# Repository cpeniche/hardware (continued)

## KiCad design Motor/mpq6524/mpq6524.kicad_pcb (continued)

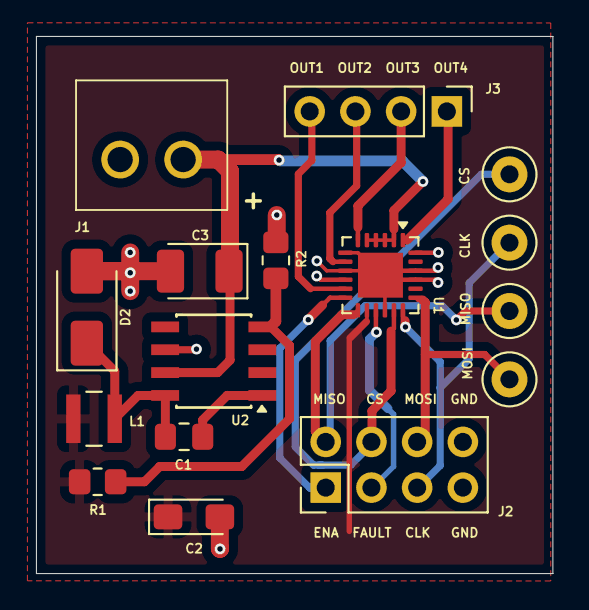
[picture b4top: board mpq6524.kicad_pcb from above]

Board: 2 copper layers, 28.7 x 29.8 mm, 16 parts (0 on the bottom side), 16 nets.

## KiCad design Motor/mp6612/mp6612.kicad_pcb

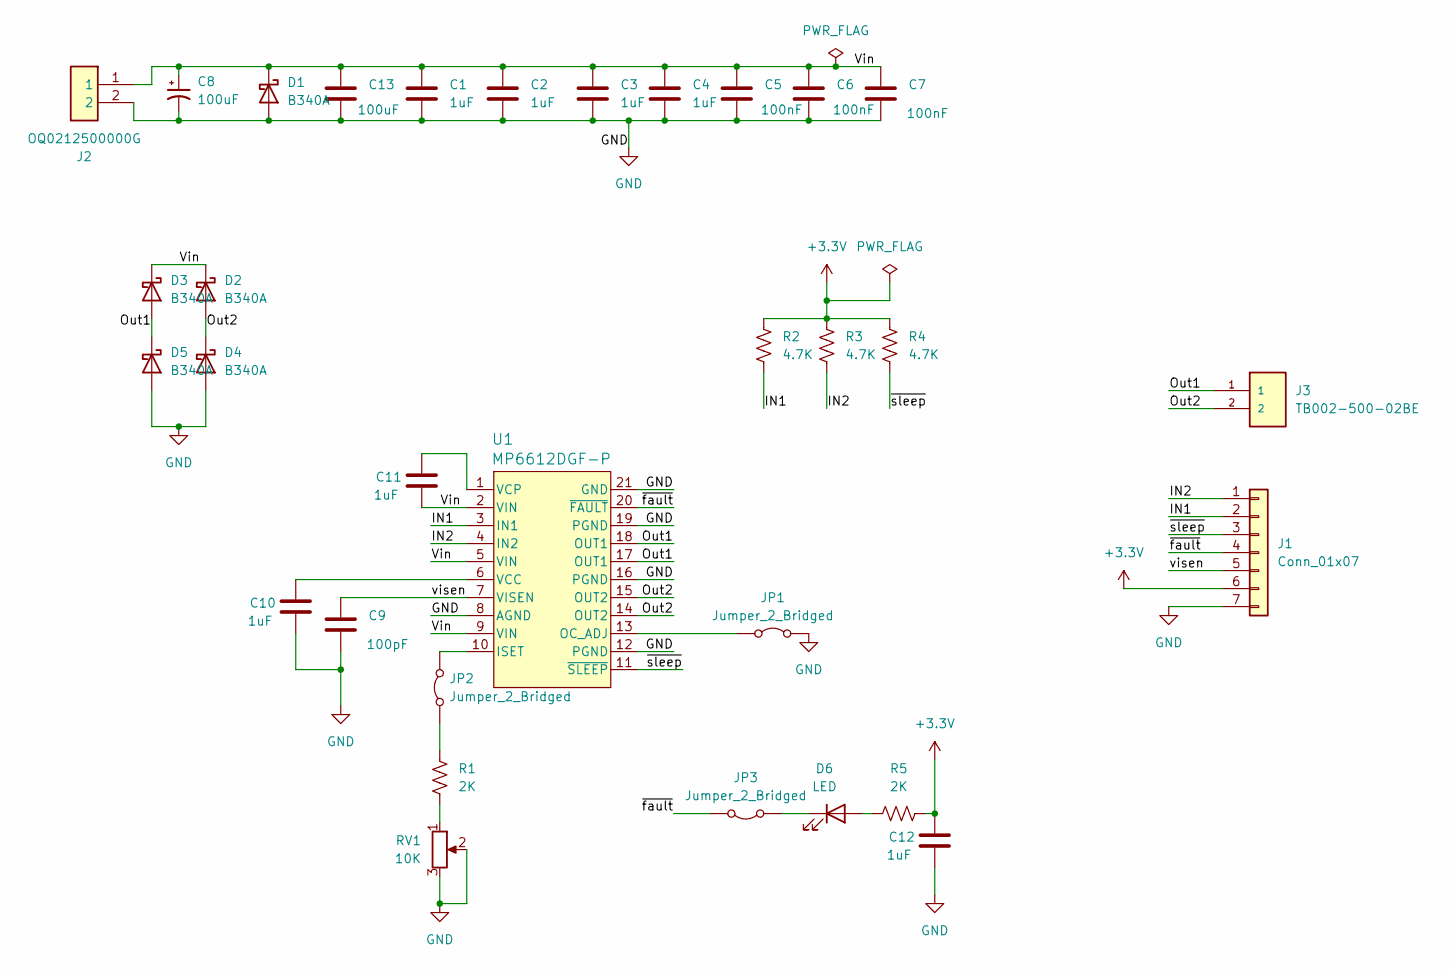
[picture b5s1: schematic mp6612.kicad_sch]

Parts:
C1, C2, C3, C4, C10, C11, C12: 1uF; C_0805_2012Metric_Pad1.18x1.45mm_HandSolder
C5, C6, C7: 100nF; C_0805_2012Metric_Pad1.18x1.45mm_HandSolder
C8: 100uF; CP_EIA-3216-18_Kemet-A_HandSolder
C9: 100pF; C_0805_2012Metric_Pad1.18x1.45mm_HandSolder
C13: 100uF; C_0805_2012Metric_Pad1.18x1.45mm_HandSolder
D1, D2, D3, D4, D5: B340A; D_SMA
D6: LED; LED_0402_1005Metric_Pad0.77x0.64mm_HandSolder
J1: Conn_01x07; PinHeader_1x07_P2.54mm_Vertical
J2: OQ0212500000G; Mouser Part Number 649-220107-C021A01LF
J3: TB002-500-02BE; CUI_TB002-500-02BE
JP1, JP2, JP3: Jumper_2_Bridged; TestPoint_2Pads_Pitch2.54mm_Drill0.8mm
R1, R5: 2K; R_0805_2012Metric_Pad1.20x1.40mm_HandSolder
R2, R3, R4: 4.7K; R_0805_2012Metric_Pad1.20x1.40mm_HandSolder
RV1: 10K; Potentiometer_Runtron_RM-065_Vertical
U1: MP6612DGF-P; TSSOP-20EP_MP6612D_MNP

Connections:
+3.3V: C12.1, J1.6, R2.2, R3.2, R4.2, R5.1
/IN1: J1.2, R2.1, U1.3 (IN1)
/IN2: J1.1, R3.1, U1.4 (IN2)
/Out1: D3.2 (A), D5.1 (K), J3.1, U1.17 (OUT1), U1.18 (OUT1)
/Out2: D2.2 (A), D4.1 (K), J3.2, U1.14 (OUT2), U1.15 (OUT2)
/Vin: C1.1, C2.1, C3.1, C4.1, C5.1, C6.1, C7.1, C8.1, C11.2, C13.1, D1.1 (K), D2.1 (K), D3.1 (K), J2.1, U1.2 (VIN), U1.5 (VIN), U1.9 (VIN)
/visen: C9.1, J1.5, U1.7 (VISEN)
/~fault: J1.4, JP3.2 (B), U1.20 (~FAULT)
/~sleep: J1.3, R4.1, U1.11 (~SLEEP)
GND: C1.2, C2.2, C3.2, C4.2, C5.2, C6.2, C7.2, C8.2, C9.2, C10.2, C12.2, C13.2, D1.2 (A), D4.2 (A), D5.2 (A), J1.7, J2.2, JP1.2 (B), RV1.2, RV1.3, U1.8 (AGND), U1.12 (PGND), U1.16 (PGND), U1.19 (PGND), U1.21 (GND)
unnamed: D6.2 (A), R5.2
unnamed: D6.1 (K), JP3.1 (A)
unnamed: JP1.1 (A), U1.13 (OC_ADJ)
unnamed: JP2.1 (A), R1.2
unnamed: JP2.2 (B), U1.10 (ISET)
unnamed: R1.1, RV1.1
unnamed: C10.1, U1.6 (VCC)
unnamed: C11.1, U1.1 (VCP)

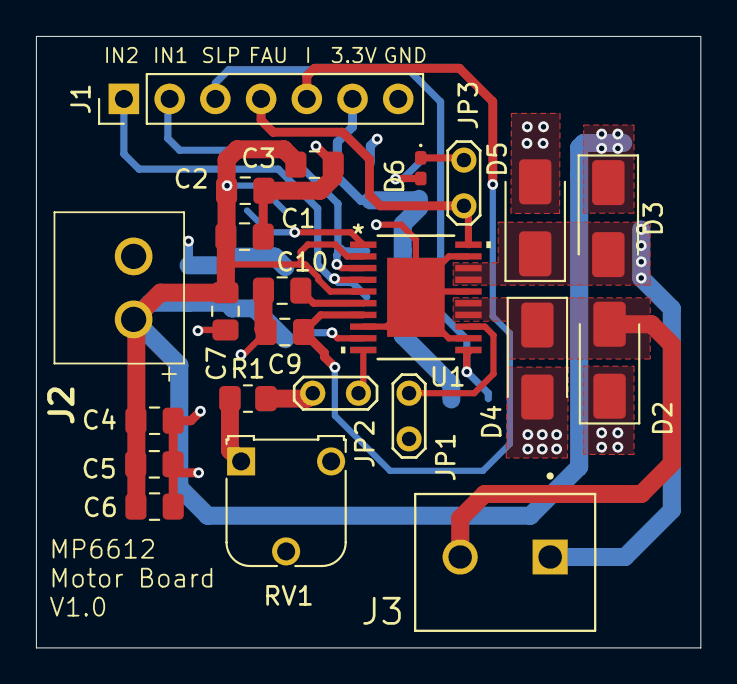
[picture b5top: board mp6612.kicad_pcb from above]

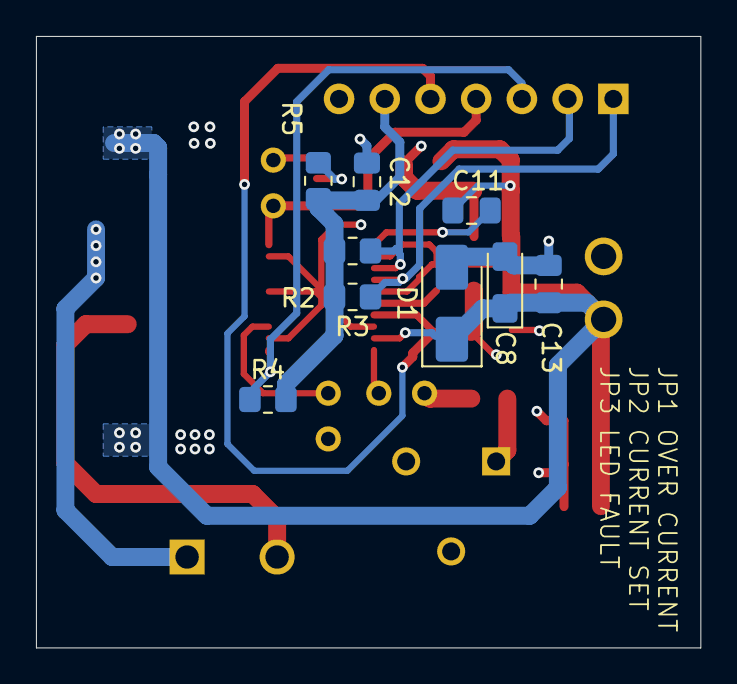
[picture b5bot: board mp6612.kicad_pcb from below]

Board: 4 copper layers, 36.9 x 34.0 mm, 32 parts (9 on the bottom side), 18 nets.

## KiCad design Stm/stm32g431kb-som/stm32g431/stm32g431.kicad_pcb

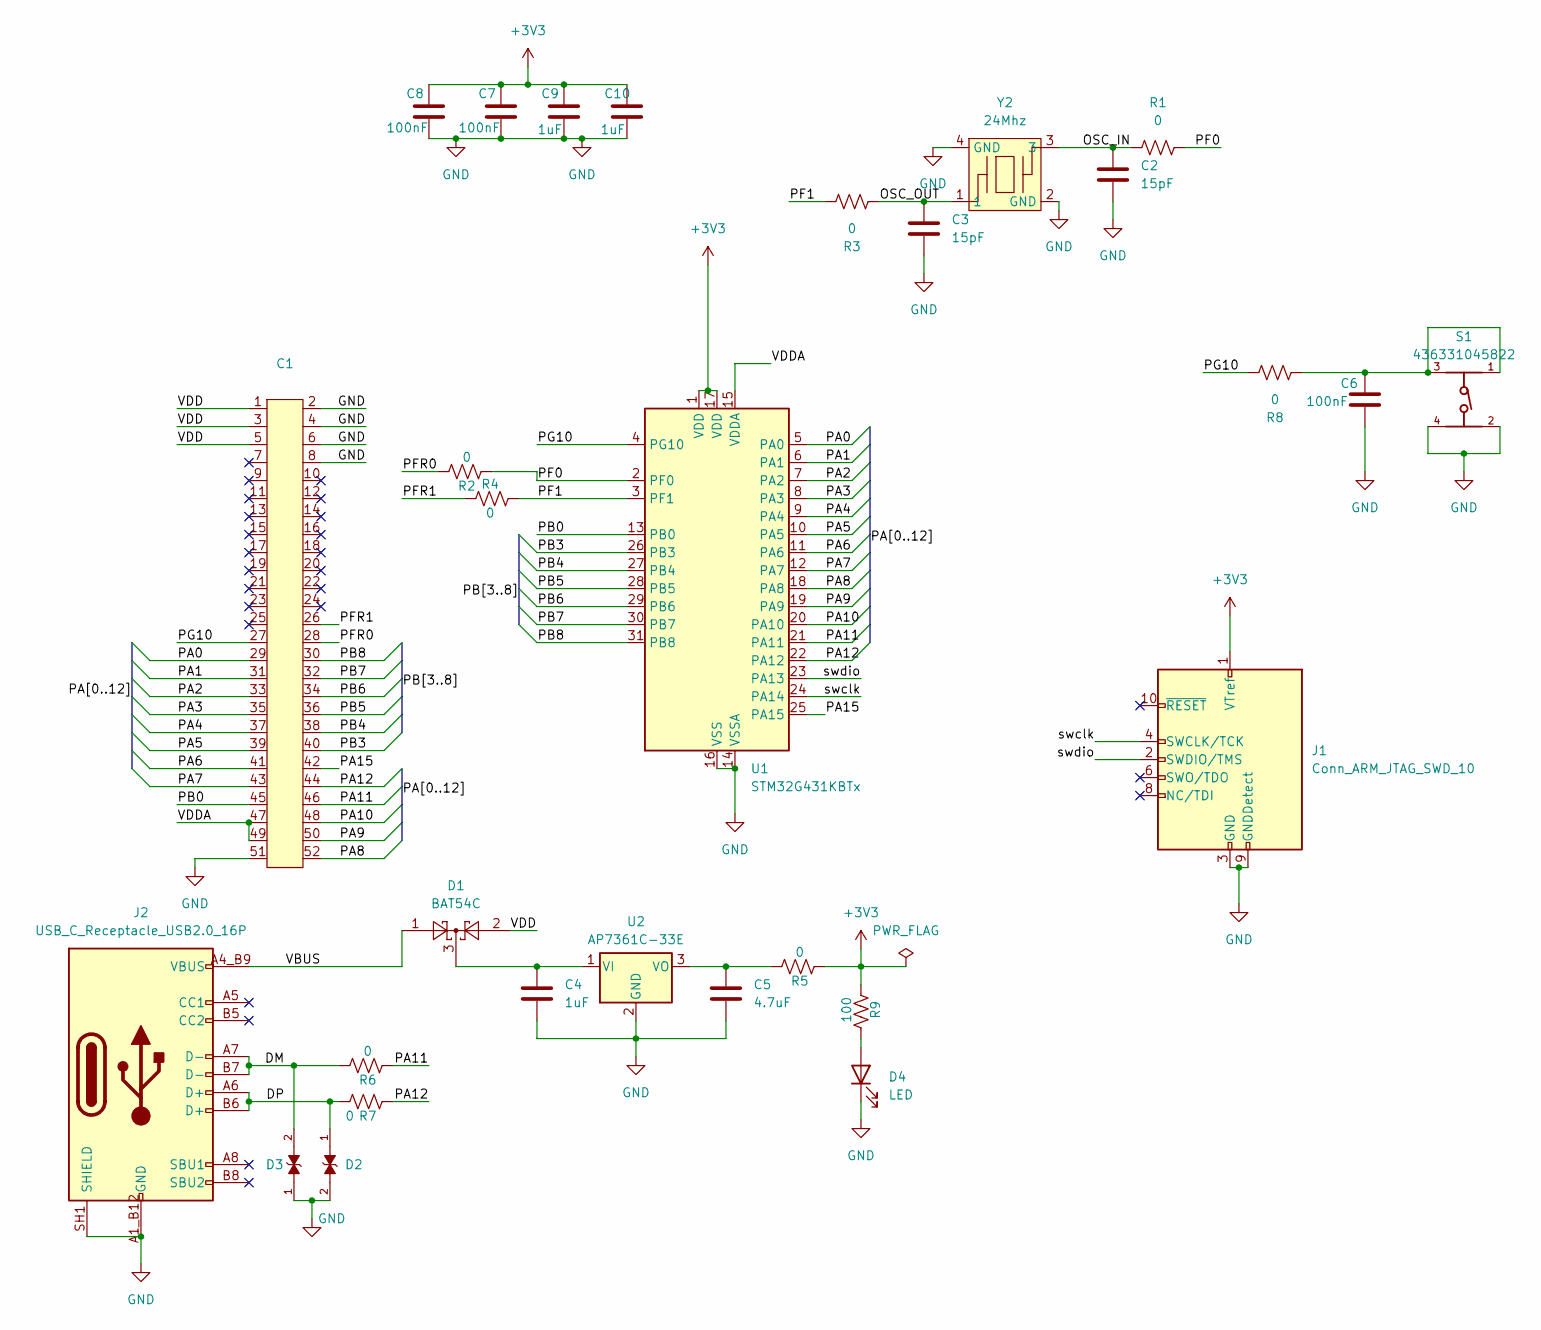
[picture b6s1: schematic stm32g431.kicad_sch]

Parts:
C1: Mini PCI express Half
C2, C3: 15pF; C_0402_1005Metric_Pad0.74x0.62mm_HandSolder
C4, C9, C10: 1uF; C_0402_1005Metric_Pad0.74x0.62mm_HandSolder
C5: 4.7uF; C_0402_1005Metric_Pad0.74x0.62mm_HandSolder
C6, C7, C8: 100nF; C_0402_1005Metric_Pad0.74x0.62mm_HandSolder
D1: BAT54C; SOT-23
D2, D3: PGB1010603NR; DIOC1608X36N
D4: LED; LED_0402_1005Metric
J1: Conn_ARM_JTAG_SWD_10; PinHeader_2x05_P1.27mm_Vertical_SMD
J2: USB_C_Receptacle_USB2.0_16P; AMPHENOL_GSB1C41110SSHR; PARTREV AX1
R1, R2, R3, R4, R5, R6, R7, R8: 0; R_0402_1005Metric_Pad0.72x0.64mm_HandSolder
R9: 100; R_0402_1005Metric_Pad0.72x0.64mm_HandSolder
S1: 436331045822; 4363X10458XX
U1: STM32G431KBTx; LQFP-32_7x7mm_P0.8mm
U2: AP7361C-33E; SOT-223-3_TabPin2
Y2: 24Mhz; jxs11

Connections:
+3V3: C7.1, C8.1, C9.1, C10.1, J1.1 (VTref), R5.2, R9.2, U1.1 (VDD), U1.17 (VDD)
/DM: D3.2, J2.A7 (D-), J2.B7 (D-), R6.1
/DP: D2.1, J2.A6 (D+), J2.B6 (D+), R7.1
/OSC_IN: C2.1, R1.1, Y2.3
/OSC_OUT: C3.1, R3.1, Y2.1
/PA0: C1.29, U1.5 (PA0)
/PA1: C1.31, U1.6 (PA1)
/PA2: C1.33, U1.7 (PA2)
/PA3: C1.35, U1.8 (PA3)
/PA4: C1.37, U1.9 (PA4)
/PA5: C1.39, U1.10 (PA5)
/PA6: C1.41, U1.11 (PA6)
/PA7: C1.43, U1.12 (PA7)
/PA8: C1.52, U1.18 (PA8)
/PA9: C1.50, U1.19 (PA9)
/PA10: C1.48, U1.20 (PA10)
/PA11: C1.46, R6.2, U1.21 (PA11)
/PA12: C1.44, R7.2, U1.22 (PA12)
/PA15: C1.42, U1.25 (PA15)
/PB0: C1.45, U1.13 (PB0)
/PB3: C1.40, U1.26 (PB3)
/PB4: C1.38, U1.27 (PB4)
/PB5: C1.36, U1.28 (PB5)
/PB6: C1.34, U1.29 (PB6)
/PB7: C1.32, U1.30 (PB7)
/PB8: C1.30, U1.31 (PB8)
/PF0: R1.2, R2.2, U1.2 (PF0)
/PF1: R3.2, R4.1, U1.3 (PF1)
/PFR0: C1.28, R2.1
/PFR1: C1.26, R4.2
/PG10: C1.27, R8.2, U1.4 (PG10)
/VBUS: D1.1, J2.A4_B9 (VBUS), J2.B4_A9 (VBUS)
/VDD: C1.1, C1.3, C1.5, D1.2
/VDDA: C1.47, C1.49, U1.15 (VDDA)
/swclk: J1.4 (SWCLK/TCK), U1.24 (PA14)
/swdio: J1.2 (SWDIO/TMS), U1.23 (PA13)
GND: C1.2, C1.4, C1.6, C1.8, C1.51, C2.2, C3.2, C4.2, C5.2, C6.2, C7.2, C8.2, C9.2, C10.2, D2.2, D3.1, D4.1 (K), J1.3 (GND), J1.5 (GND), J1.9 (GNDDetect), J2.A1_B12 (GND), J2.B1_A12 (GND), J2.SH1 (SHIELD), S1.2, S1.4, U1.14 (VSSA), U1.16 (VSS), U1.32 (VSS), U2.2 (GND), Y2.2 (GND), Y2.4 (GND)
unnamed: C6.1, R8.1, S1.1, S1.3
unnamed: D4.2 (A), R9.1
unnamed: C4.1, D1.3, U2.1 (VI)
unnamed: C5.1, R5.1, U2.3 (VO)

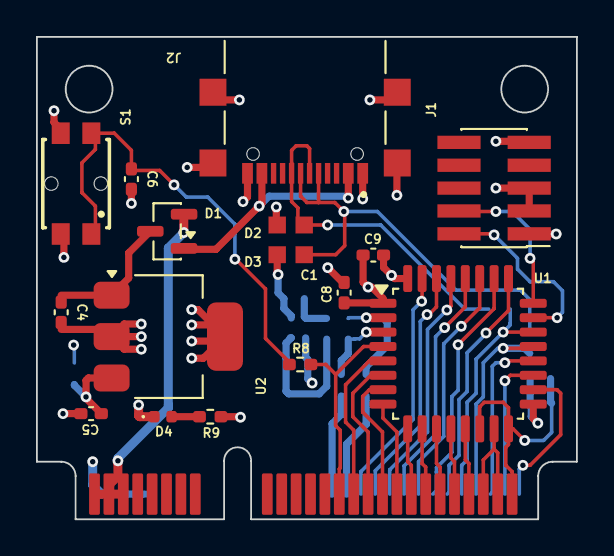
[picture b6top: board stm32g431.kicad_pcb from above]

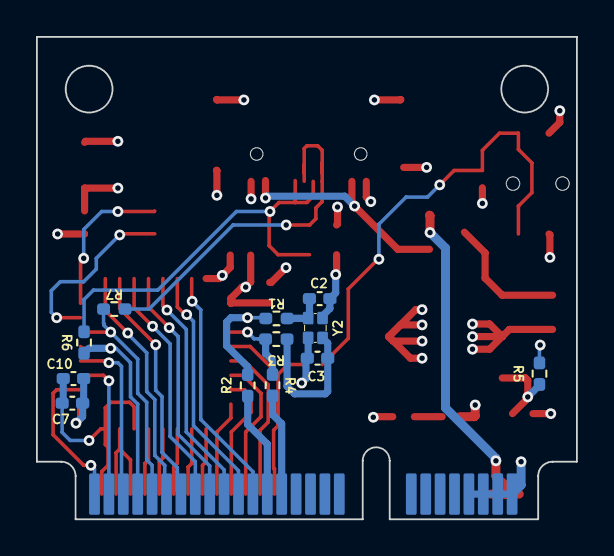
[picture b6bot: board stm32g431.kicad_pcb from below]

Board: 4 copper layers, 30.0 x 26.8 mm, 29 parts (12 on the bottom side), 41 nets.

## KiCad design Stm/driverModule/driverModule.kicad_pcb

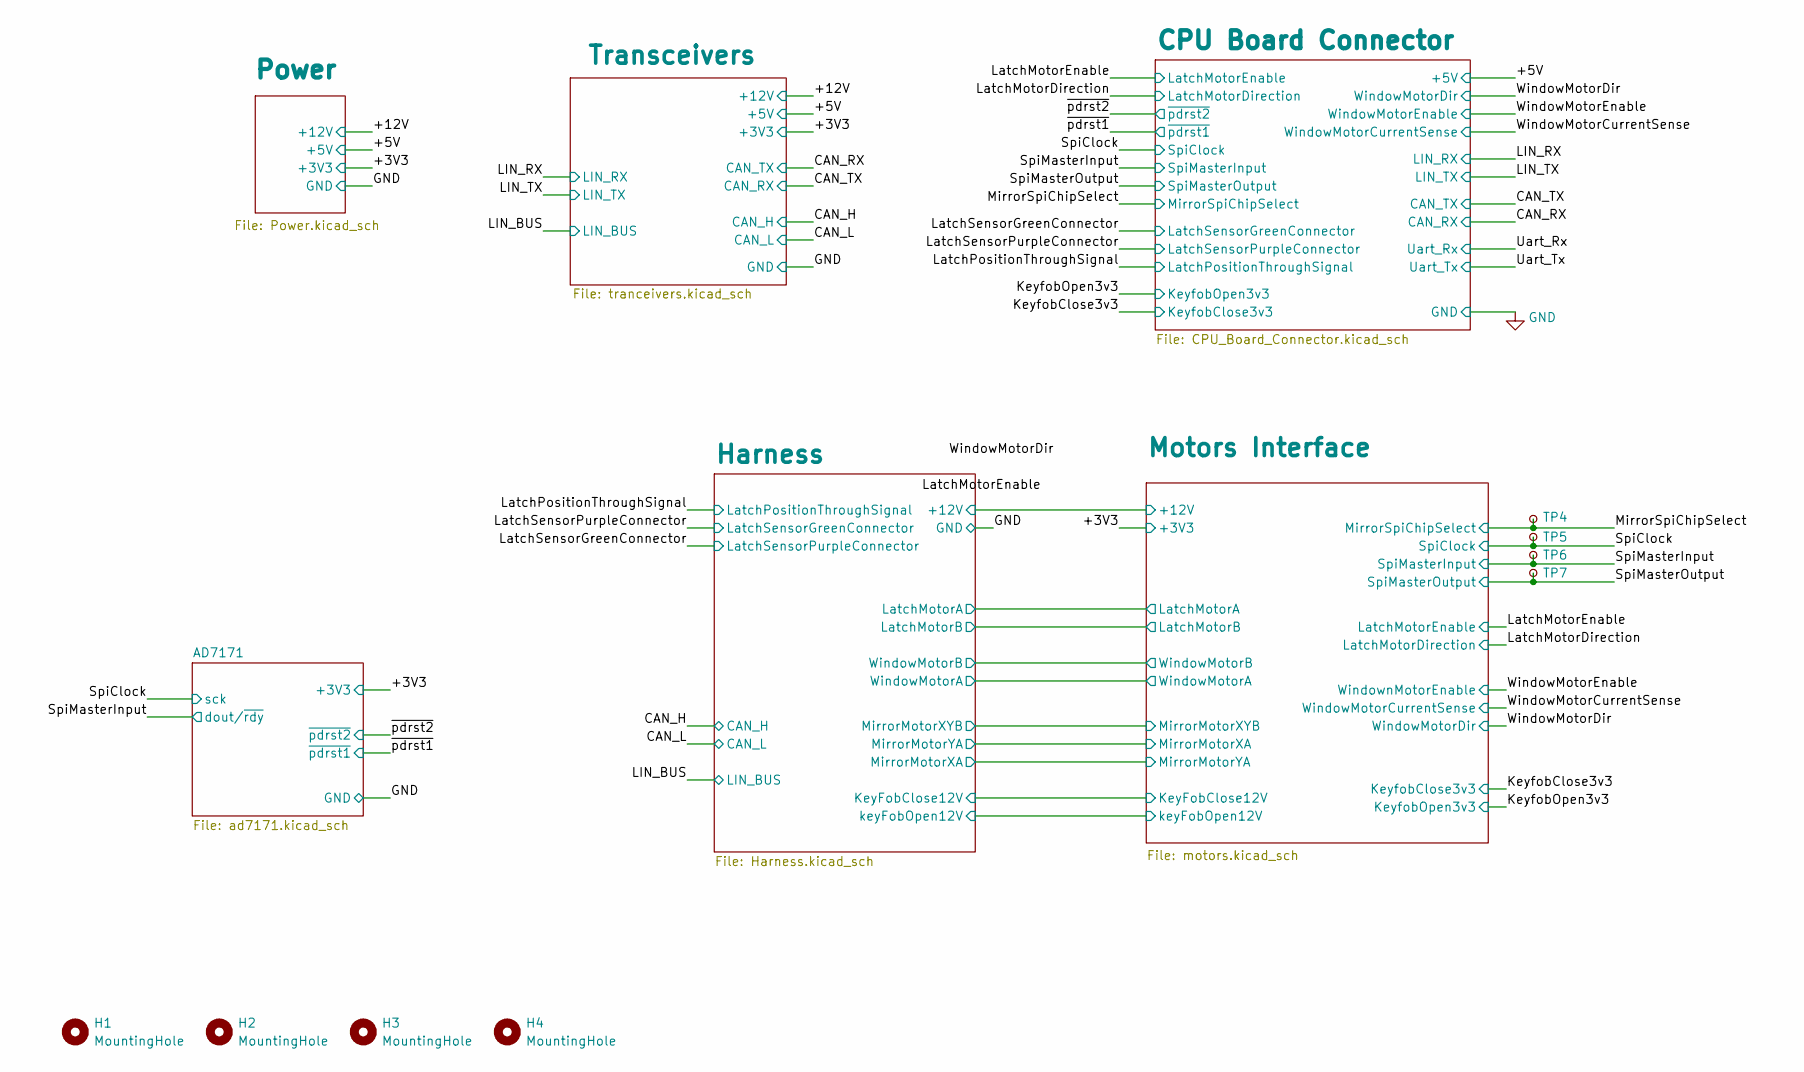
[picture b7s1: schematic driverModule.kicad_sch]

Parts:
H1, H2, H3, H4: MountingHole; MountingHole_2.2mm_M2
TP4, TP5, TP6, TP7: TestPoint_Small; TestPoint_Pad_1.0x1.0mm

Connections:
/MirrorSpiChipSelect: TP4.1; also elsewhere on the board
/SpiClock: TP5.1; also elsewhere on the board
/SpiMasterInput: TP6.1; also elsewhere on the board
/SpiMasterOutput: TP7.1; also elsewhere on the board

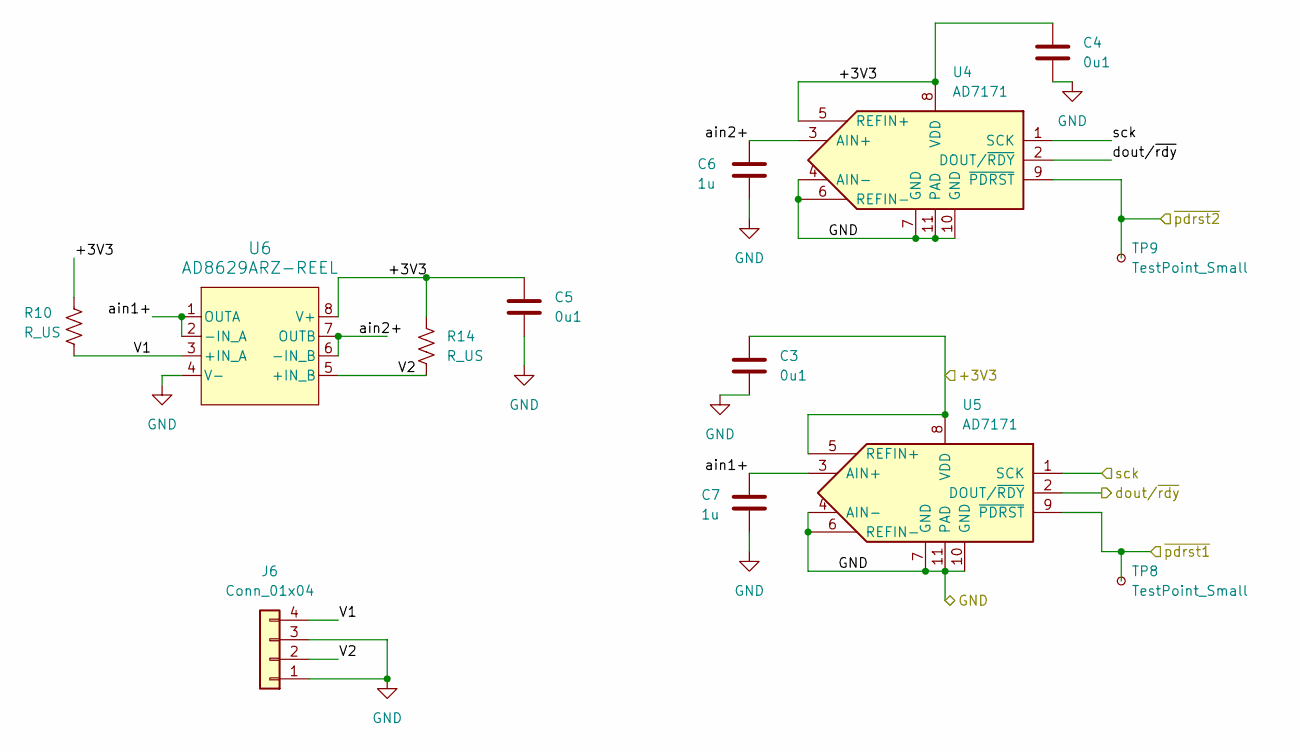
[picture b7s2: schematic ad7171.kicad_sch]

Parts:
C3, C4, C5: 0u1; C_0402_1005Metric_Pad0.74x0.62mm_HandSolder
C6, C7: 1u; C_0402_1005Metric_Pad0.74x0.62mm_HandSolder
J6: Conn_01x04; JST_EH_B4B-EH-A_1x04_P2.50mm_Vertical
R10, R14: R_US; R_0402_1005Metric_Pad0.72x0.64mm_HandSolder
TP8, TP9: TestPoint_Small; TestPoint_Pad_1.0x1.0mm
U4, U5: AD7171; DFN-10-1EP_3x3mm_P0.5mm_EP1.55x2.48mm
U6: AD8629ARZ-REEL; SOIC-8_5.3x5.3mm_P1.27mm

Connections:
+3V3: C3.1, C4.1, C5.1, R10.1, R14.1, U4.5 (REFIN+), U4.8 (VDD), U5.5 (REFIN+), U5.8 (VDD), U6.8 (V+); also elsewhere on the board
/AD7171/V1: J6.4, R10.2, U6.3 (+IN_A)
/AD7171/V2: J6.2, R14.2, U6.5 (+IN_B)
/AD7171/ain1+: C7.1, U5.3 (AIN+), U6.1 (OUTA), U6.2 (-IN_A)
/AD7171/ain2+: C6.1, U4.3 (AIN+), U6.6 (-IN_B), U6.7 (OUTB)
/SpiClock: U4.1 (SCK), U5.1 (SCK); also elsewhere on the board
/SpiMasterInput: U4.2 (DOUT/~RDY), U5.2 (DOUT/~RDY); also elsewhere on the board
/~pdrst1: TP8.1, U5.9 (~PDRST); also elsewhere on the board
/~pdrst2: TP9.1, U4.9 (~PDRST); also elsewhere on the board
GND: C3.2, C4.2, C5.2, C6.2, C7.2, J6.1, J6.3, U4.4 (AIN-), U4.6 (REFIN-), U4.7 (GND), U4.10 (GND), U4.11 (PAD), U5.4 (AIN-), U5.6 (REFIN-), U5.7 (GND), U5.10 (GND), U5.11 (PAD), U6.4 (V-); also elsewhere on the board

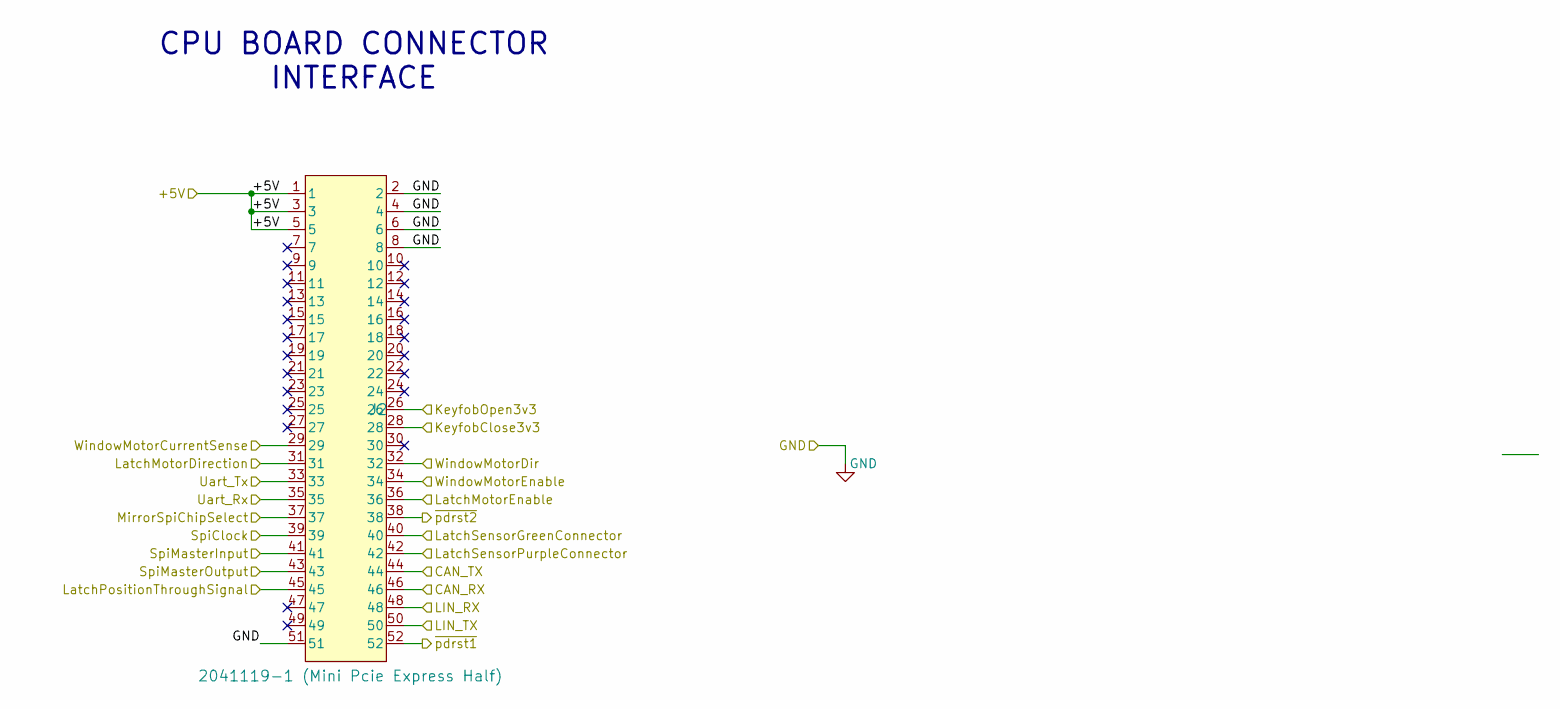
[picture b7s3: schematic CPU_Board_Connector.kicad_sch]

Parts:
J2: 2041119-1 (Mini Pcie Express Half); CONN_2041119-1_TEC

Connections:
+5V: J2.1, J2.3, J2.5; also elsewhere on the board
/CAN_RX: J2.46; also elsewhere on the board
/CAN_TX: J2.44; also elsewhere on the board
/KeyfobClose3v3: J2.28; also elsewhere on the board
/KeyfobOpen3v3: J2.26; also elsewhere on the board
/LIN_RX: J2.48; also elsewhere on the board
/LIN_TX: J2.50; also elsewhere on the board
/LatchMotorDirection: J2.31; also elsewhere on the board
/LatchMotorEnable: J2.36; also elsewhere on the board
/LatchPositionThroughSignal: J2.45; also elsewhere on the board
/LatchSensorGreenConnector: J2.40; also elsewhere on the board
/LatchSensorPurpleConnector: J2.42; also elsewhere on the board
/MirrorSpiChipSelect: J2.37; also elsewhere on the board
/SpiClock: J2.39; also elsewhere on the board
/SpiMasterInput: J2.41; also elsewhere on the board
/SpiMasterOutput: J2.43; also elsewhere on the board
/Uart_Rx: J2.35
/Uart_Tx: J2.33
/WindowMotorCurrentSense: J2.29; also elsewhere on the board
/WindowMotorDir: J2.32; also elsewhere on the board
/WindowMotorEnable: J2.34; also elsewhere on the board
/~pdrst1: J2.52; also elsewhere on the board
/~pdrst2: J2.38; also elsewhere on the board
GND: J2.2, J2.4, J2.6, J2.8, J2.51; also elsewhere on the board

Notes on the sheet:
CPU BOARD CONNECTOR INTERFACE

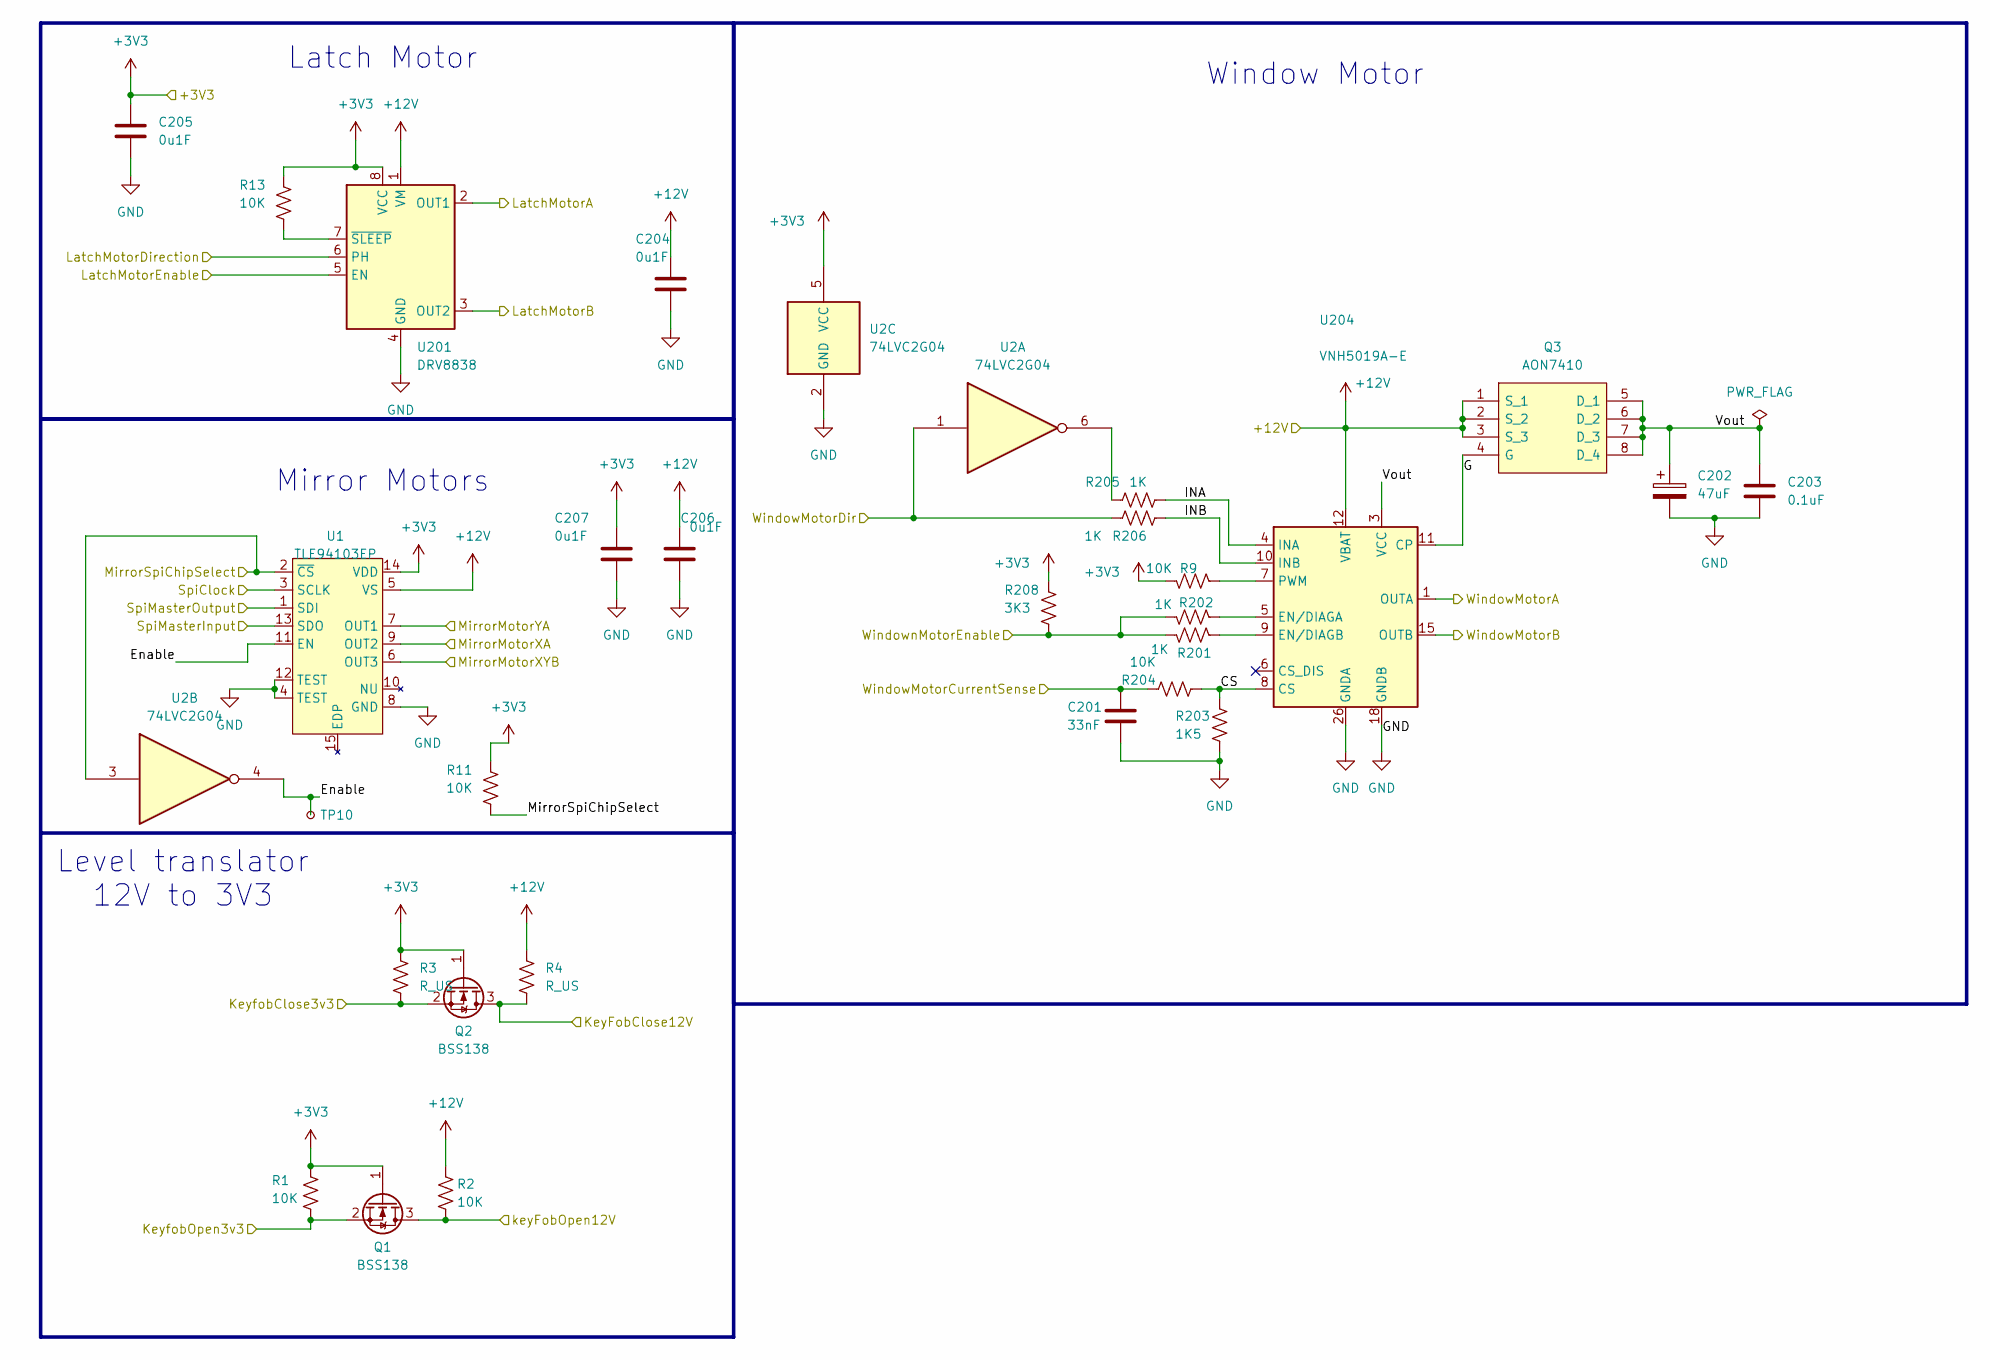
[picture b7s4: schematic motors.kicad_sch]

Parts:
C201: 33nF; C_0805_2012Metric
C202: 47uF; CP_EIA-6032-15_Kemet-U
C203: 0.1uF; C_0402_1005Metric_Pad0.74x0.62mm_HandSolder
C204, C205, C206, C207: 0u1F; C_0402_1005Metric_Pad0.74x0.62mm_HandSolder
Q1, Q2: BSS138; SOT-23
Q3: AON7410; DFN_3X3_EP; Manufacturer_Part_Number AON7410
R1, R2, R9, R11, R13, R204: 10K; R_0402_1005Metric_Pad0.72x0.64mm_HandSolder
R3, R4: R_US; R_0402_1005Metric_Pad0.72x0.64mm_HandSolder
R201, R202, R205, R206: 1K; R_0402_1005Metric_Pad0.72x0.64mm_HandSolder
R203: 1K5; R_0402_1005Metric_Pad0.72x0.64mm_HandSolder
R208: 3K3; R_0402_1005Metric_Pad0.72x0.64mm_HandSolder
TP10: TestPoint_Small; TestPoint_Pad_1.0x1.0mm
U1: TLE94103EP; Infineon_PG-TSDSO-14-22
U2: 74LVC2G04; SOT-363_SC-70-6
U201: DRV8838; WSON-8-1EP_2x2mm_P0.5mm_EP0.9x1.6mm
U204: VNH5019A-E; ST_MultiPowerSO-30

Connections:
+3V3: C205.1, C207.1, Q1.1 (G), Q2.1 (G), R1.1, R3.1, R9.1, R11.1, R13.1, R208.1, U1.14 (VDD), U2.5 (VCC), U201.8 (VCC); also elsewhere on the board
+12V: C204.1, C206.1, Q3.1 (S_1), Q3.2 (S_2), Q3.3 (S_3), R2.1, R4.1, U1.5 (VS), U201.1 (VM), U204.12 (VBAT); also elsewhere on the board
/Harness/KeyFobClose12V: Q2.3 (D), R4.2; also elsewhere on the board
/Harness/LatchMotorA: U201.2 (OUT1); also elsewhere on the board
/Harness/LatchMotorB: U201.3 (OUT2); also elsewhere on the board
/Harness/MirrorMotorXA: U1.7 (OUT1); also elsewhere on the board
/Harness/MirrorMotorXYB: U1.6 (OUT3); also elsewhere on the board
/Harness/MirrorMotorYA: U1.9 (OUT2); also elsewhere on the board
/Harness/WindowMotorA: U204.1 (OUTA), U204.25 (OUTA), U204.30 (OUTA), U204.33 (OUTA); also elsewhere on the board
/Harness/WindowMotorB: U204.15 (OUTB), U204.16 (OUTB), U204.21 (OUTB), U204.32 (OUTB); also elsewhere on the board
/Harness/keyFobOpen12V: Q1.3 (D), R2.2; also elsewhere on the board
/KeyfobClose3v3: Q2.2 (S), R3.2; also elsewhere on the board
/KeyfobOpen3v3: Q1.2 (S), R1.2; also elsewhere on the board
/LatchMotorDirection: U201.6 (PH); also elsewhere on the board
/LatchMotorEnable: U201.5 (EN); also elsewhere on the board
/MirrorSpiChipSelect: R11.2, U1.2 (~CS), U2.3; also elsewhere on the board
/Motors Interface/CS: R203.1, R204.2, U204.8 (CS)
/Motors Interface/Enable: TP10.1, U1.11 (EN), U2.4
/Motors Interface/G: Q3.4 (G), U204.11 (CP)
/Motors Interface/INA: R205.2, U204.4 (INA)
/Motors Interface/INB: R206.2, U204.10 (INB)
/Motors Interface/Vout: C202.1, C203.1, Q3.5 (D_1), Q3.6 (D_2), Q3.7 (D_3), Q3.8 (D_4), U204.3 (VCC), U204.13 (VCC), U204.23 (VCC), U204.31 (VCC)
/SpiClock: U1.3 (SCLK); also elsewhere on the board
/SpiMasterInput: U1.13 (SDO); also elsewhere on the board
/SpiMasterOutput: U1.1 (SDI); also elsewhere on the board
/WindowMotorCurrentSense: C201.1, R204.1; also elsewhere on the board
/WindowMotorDir: R206.1, U2.1; also elsewhere on the board
/WindowMotorEnable: R201.1, R202.1, R208.2; also elsewhere on the board
GND: C201.2, C202.2, C203.2, C204.2, C205.2, C206.2, C207.2, R203.2, U1.4 (TEST), U1.8 (GND), U1.12 (TEST), U2.2 (GND), U201.4 (GND), U201.9 (GND), U204.18 (GNDB), U204.19 (GNDB), U204.20 (GNDB), U204.26 (GNDA), U204.27 (GNDA), U204.28 (GNDA); also elsewhere on the board
unnamed: R205.1, U2.6
unnamed: R13.2, U201.7 (~SLEEP)
unnamed: R202.2, U204.5 (EN/DIAGA)
unnamed: R201.2, U204.9 (EN/DIAGB)
unnamed: R9.2, U204.7 (PWM)

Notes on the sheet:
Level translator 12V to 3V3
Mirror Motors
Latch Motor
Window Motor

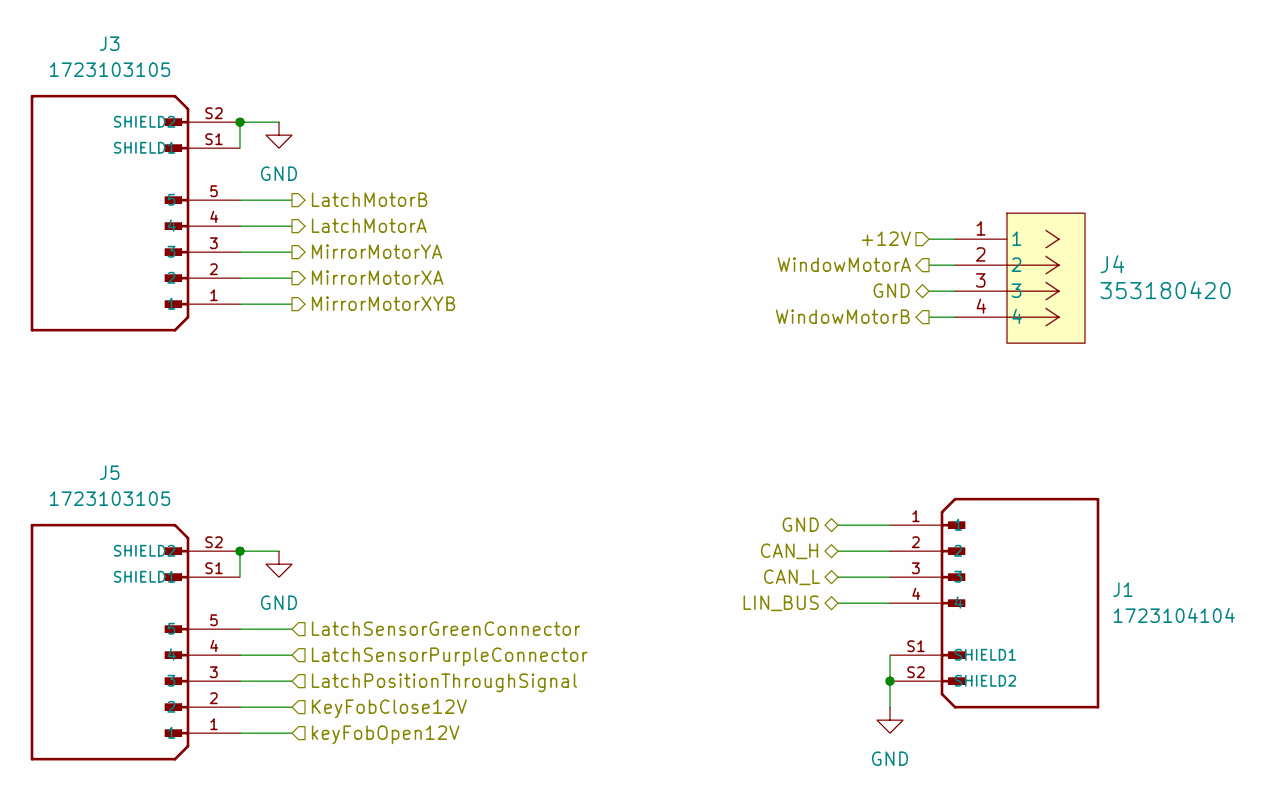
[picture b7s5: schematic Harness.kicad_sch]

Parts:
J1: 1723104104; MOLEX_1723104104; PARTREV with Solder Nail, 3.50mm Pitch, Single 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
J3, J5: 1723103105; MOLEX_1723103105; PARTREV B1
J4: 353180420; CONN_35318-0420_MOL

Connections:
+12V: J4.1; also elsewhere on the board
/CAN_H: J1.2; also elsewhere on the board
/CAN_L: J1.3; also elsewhere on the board
/Harness/KeyFobClose12V: J5.2; also elsewhere on the board
/Harness/LatchMotorA: J3.4; also elsewhere on the board
/Harness/LatchMotorB: J3.5; also elsewhere on the board
/Harness/MirrorMotorXA: J3.2; also elsewhere on the board
/Harness/MirrorMotorXYB: J3.1; also elsewhere on the board
/Harness/MirrorMotorYA: J3.3; also elsewhere on the board
/Harness/WindowMotorA: J4.2; also elsewhere on the board
/Harness/WindowMotorB: J4.4; also elsewhere on the board
/Harness/keyFobOpen12V: J5.1; also elsewhere on the board
/LIN_BUS: J1.4; also elsewhere on the board
/LatchPositionThroughSignal: J5.3; also elsewhere on the board
/LatchSensorGreenConnector: J5.4; also elsewhere on the board
/LatchSensorPurpleConnector: J5.5; also elsewhere on the board
GND: J1.1, J1.S1 (SHIELD1), J1.S2 (SHIELD2), J3.S1 (SHIELD1), J3.S2 (SHIELD2), J4.3, J5.S1 (SHIELD1), J5.S2 (SHIELD2); also elsewhere on the board

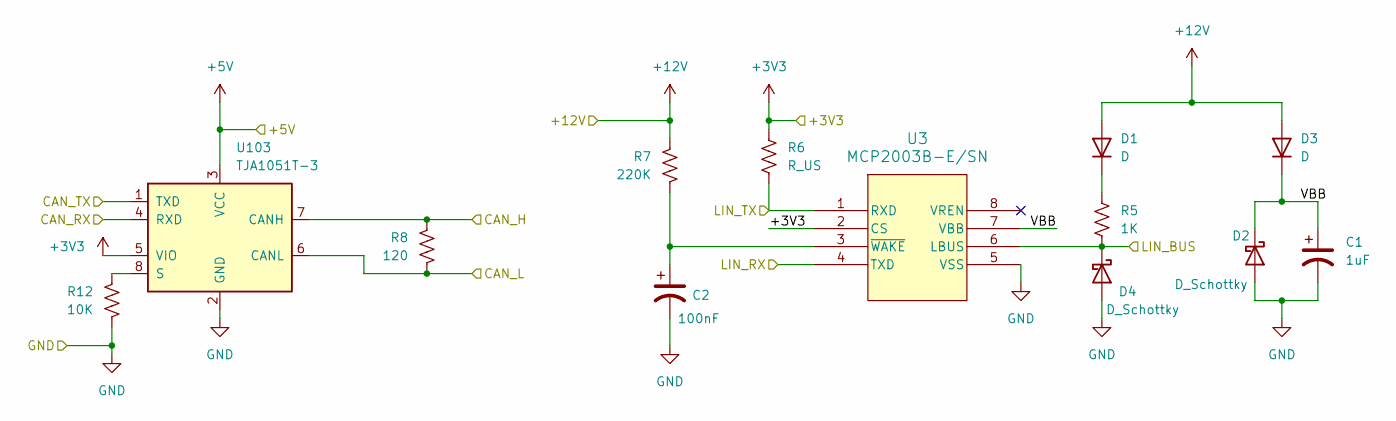
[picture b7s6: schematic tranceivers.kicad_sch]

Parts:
C1: 1uF; C_0402_1005Metric
C2: 100nF; C_0402_1005Metric
D1, D3: D; D_0402_1005Metric
D2, D4: D_Schottky; D_0402_1005Metric
R5: 1K; R_0402_1005Metric
R6: R_US; R_0402_1005Metric
R7: 220K; R_0402_1005Metric
R8: 120; R_0402_1005Metric
R12: 10K; R_0402_1005Metric
U3: MCP2003B-E/SN; SOIC8_SN_MCH
U103: TJA1051T-3; SOIC-8_3.9x4.9mm_P1.27mm

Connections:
+3V3: R6.1, U3.2 (CS), U103.5 (VIO); also elsewhere on the board
+5V: U103.3 (VCC); also elsewhere on the board
+12V: D1.2 (A), D3.2 (A), R7.1; also elsewhere on the board
/CAN_H: R8.1, U103.7 (CANH); also elsewhere on the board
/CAN_L: R8.2, U103.6 (CANL); also elsewhere on the board
/CAN_RX: U103.1 (TXD); also elsewhere on the board
/CAN_TX: U103.4 (RXD); also elsewhere on the board
/LIN_BUS: D4.1 (K), R5.2, U3.6 (LBUS); also elsewhere on the board
/LIN_RX: U3.4 (TXD); also elsewhere on the board
/LIN_TX: R6.2, U3.1 (RXD); also elsewhere on the board
/Transceivers/VBB: C1.1, D2.1 (K), D3.1 (K), U3.7 (VBB)
GND: C1.2, C2.2, D2.2 (A), D4.2 (A), R12.2, U3.5 (VSS), U103.2 (GND); also elsewhere on the board
unnamed: D1.1 (K), R5.1
unnamed: C2.1, R7.2, U3.3 (~WAKE)
unnamed: R12.1, U103.8 (S)
